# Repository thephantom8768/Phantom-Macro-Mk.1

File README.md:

# Phantom Macro Mk.1 Series

> A modular, snap-together macropad ecosystem with lateral pogo-pin bus interconnects.

Chain modules side-by-side to expand your desktop workflow—from a compact macro-pad into a full fledge keyboard.

---

## 📌 Project Status

- **Hardware:** Series still in-dev
- **Firmware:** In active development.
- **Interconnect:** Custom edge-mount 8 pin pogo interface.

---

## ⚡ Features

- **Snap & Chain Topology:** Expand your layout horizontally by mating adjacent modules using edge-mounted pogo connectors.
- **Unified Bus Standard:** Standardized power, ground, and communication rails allow any Mk.1-series compatible module to hot-mate with the system.
- **Flexible Layouts:** Mix and match different form factors (numpads, macro clusters, encoder dials) without rerunning separate USB cables to your host machine.

## ⚠️ Build Warnings

> **DIY Soldering Required:** This is a fully self-assembled project. It is not a plug-and-play kit and requires intermediate soldering experience.

* **Double-Sided Assembly:** Depending on the macro-pad, components might need to be soldered onto **both the top and bottom** of the PCB.

## *Mk.1 Series*

<details>
  <summary><b>🔢 Phantom-Macro-Mk.1 Pad (click here)</b></summary>
  
  ### Macro Mk.1 Pad
  
  #### Schematic

<table>
  <tr>
    <td colspan="4">
      
    </td>
  </tr>
</table>

#### PCB Layout

4 Layers PCB
| Front (1st layer)|Back (4th layer) |
| ----- | ----- |
|  |  |

#### PCB
| Front | Back |
| ----- | ---- |
|  |  |
|  |  |

#### Case

</details>

<details>
  <summary><b>🎹 Phantom-Macro-Mk.1 MIDI (click here)</b></summary>
  
  ### Macro Mk.1 MIDI
  
  #### Schematic

  ### PCB Layout 

  2 Layers PCB
  | Front | Back |
  | ----- | ----- |
  |  |  |

  #### PCB
  | Front | Back |
  | ----- | ---- |
  |  |  |
  |  |  |

</details>

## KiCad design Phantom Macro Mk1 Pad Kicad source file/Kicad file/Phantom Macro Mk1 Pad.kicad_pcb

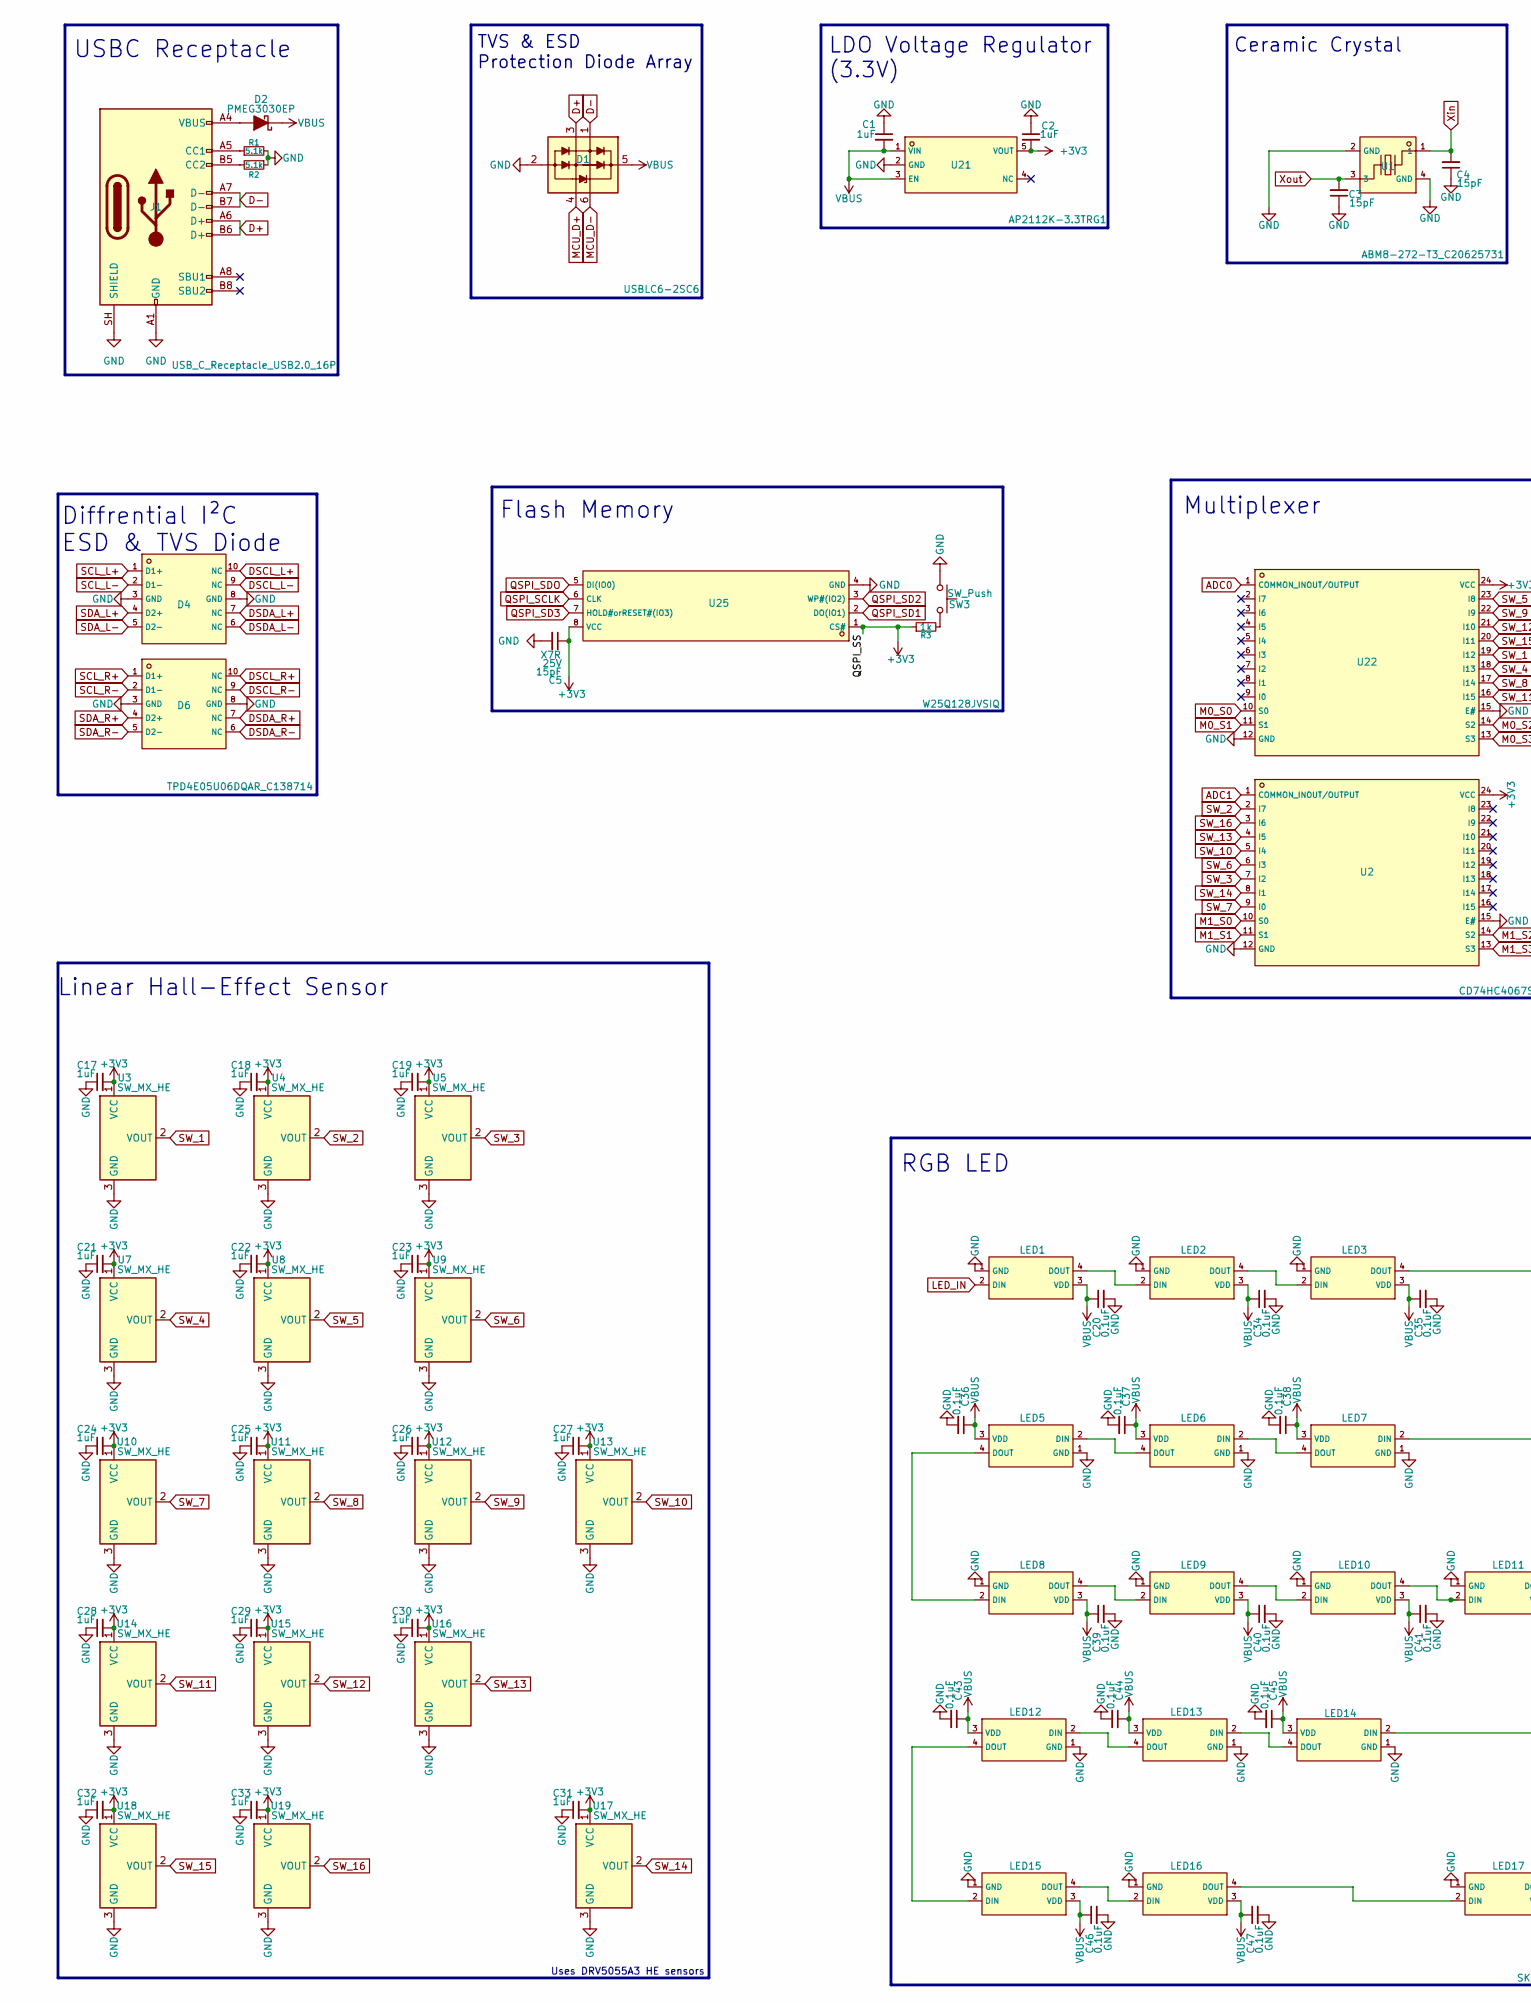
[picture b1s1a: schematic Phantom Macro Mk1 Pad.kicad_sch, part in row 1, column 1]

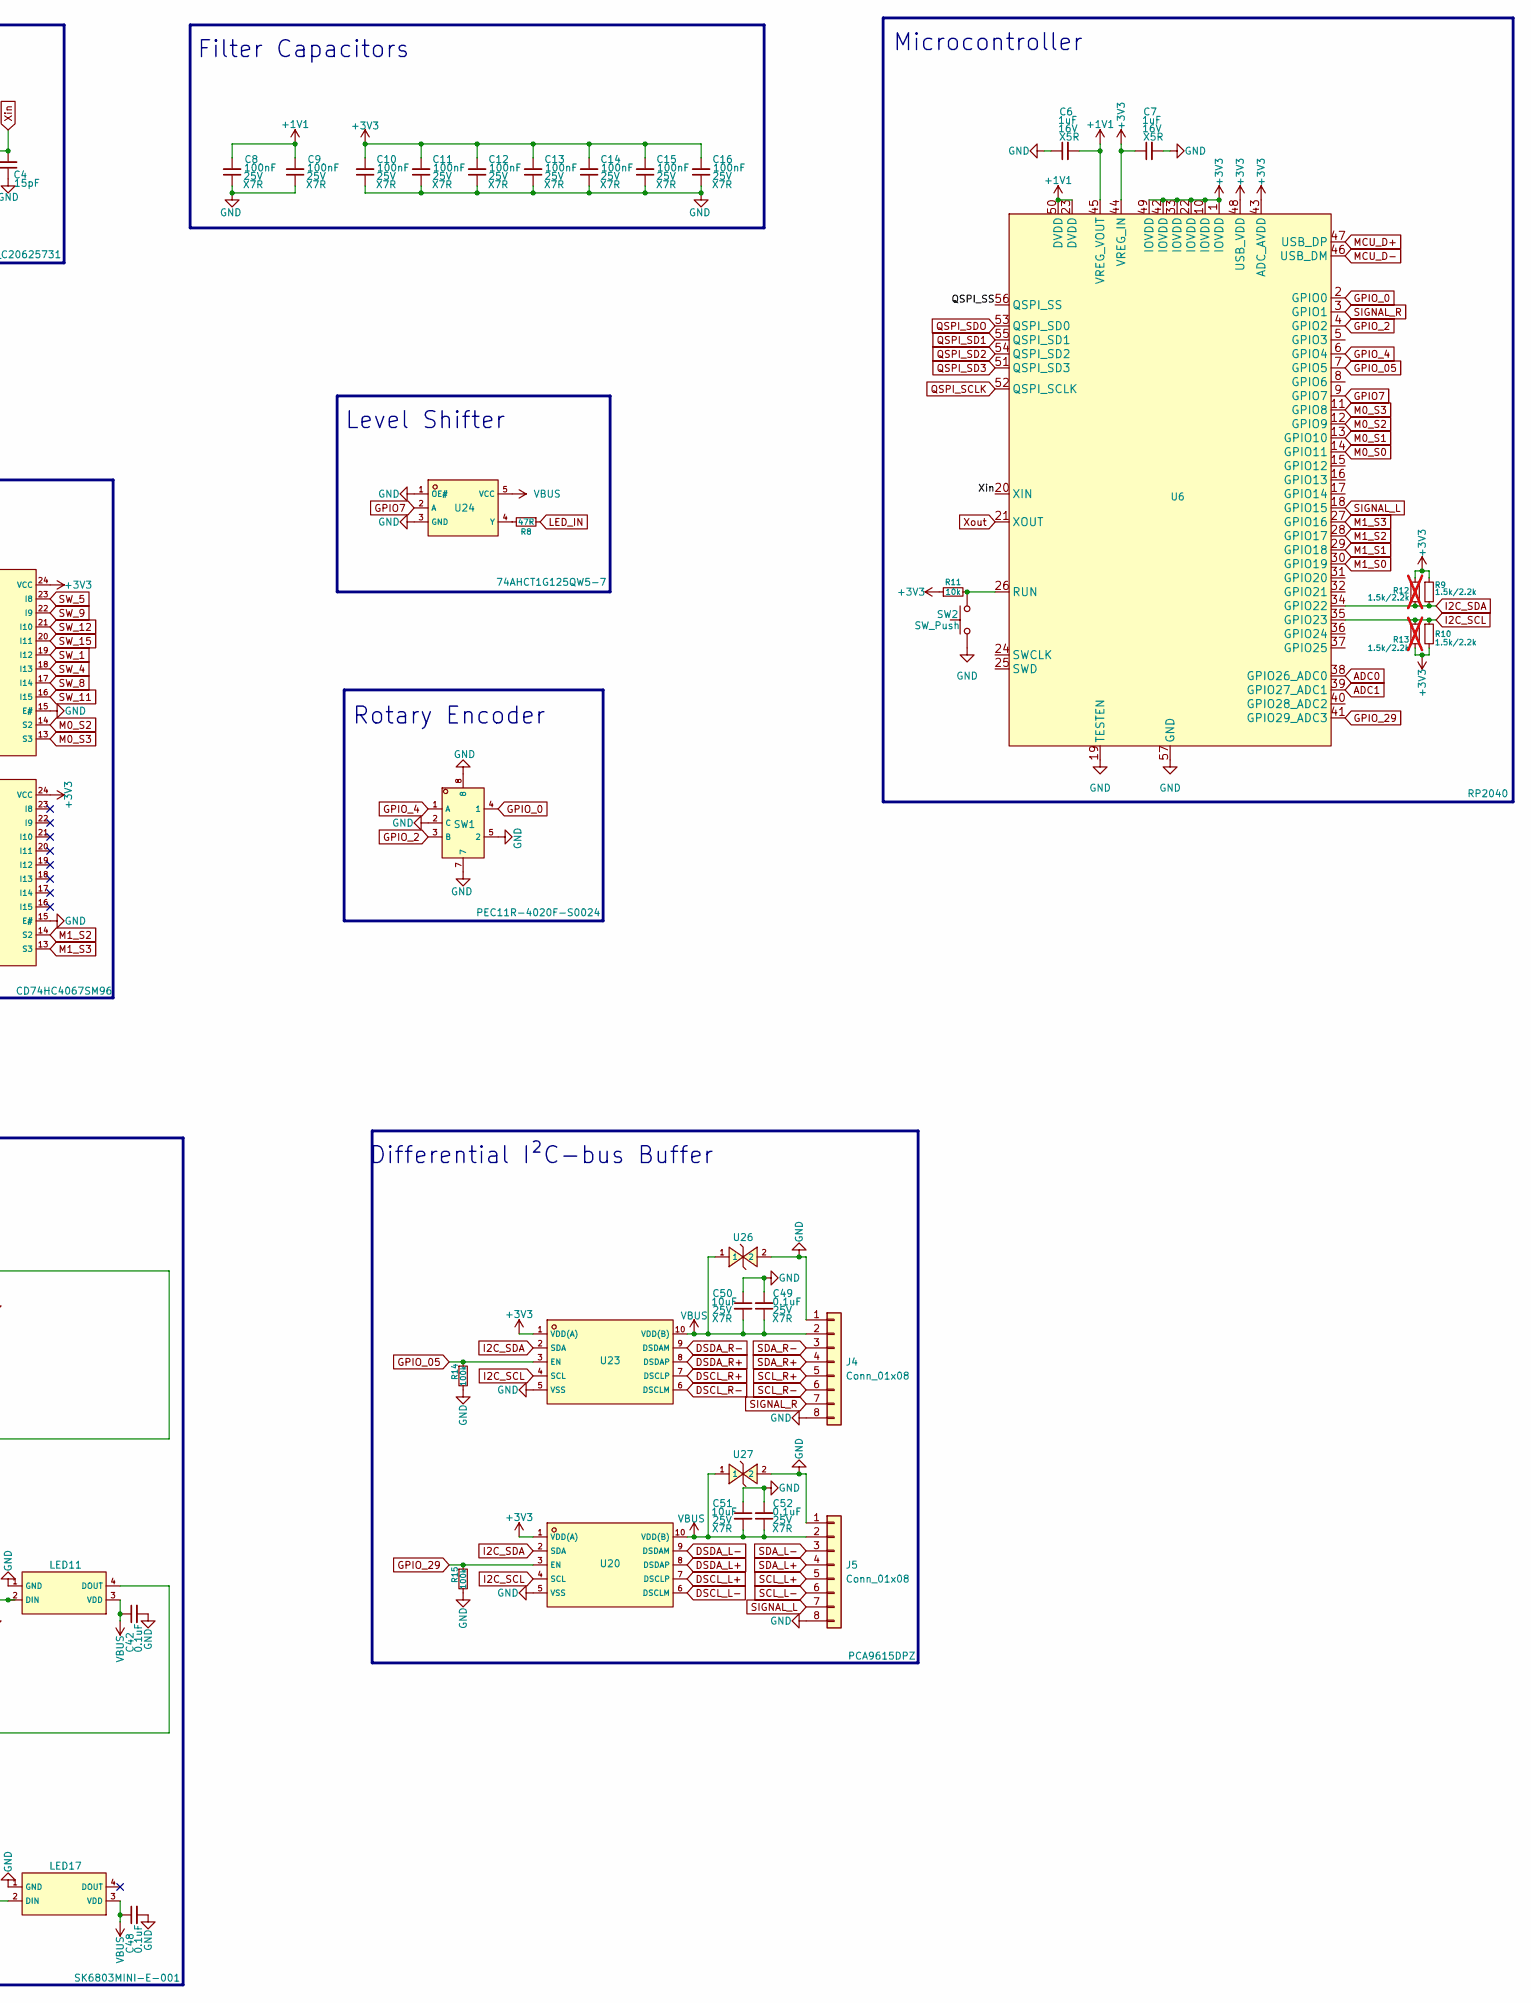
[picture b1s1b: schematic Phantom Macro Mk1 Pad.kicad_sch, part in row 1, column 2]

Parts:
C1, C2, C17, C18, C19, C21, C22, C23, C24, C25, C26, C27, C28, C29, C30, C31, C32, C33: 1uF; C_0603_1608Metric_Pad1.08x0.95mm_HandSolder
C3, C4: 15pF; C_0402_1005Metric_Pad0.74x0.62mm_HandSolder
C5: 15pF; C_0402_1005Metric_Pad0.74x0.62mm_HandSolder; Rating 25V
C6, C7: 1uF; C_0603_1608Metric_Pad1.08x0.95mm_HandSolder; Rating 16V
C8, C9, C10, C11, C12, C13, C14, C15, C16: 100nF; C_0402_1005Metric_Pad0.74x0.62mm_HandSolder; Rating 25V
C20, C34, C35, C36, C37, C38, C39, C40, C41, C42, C43, C44, C45, C46, C47, C48: 0.1uF; C_0603_1608Metric_Pad1.08x0.95mm_HandSolder
C49, C52: 0.1uF; C_0805_2012Metric_Pad1.18x1.45mm_HandSolder; Rating 25V
C50, C51: 10uF; C_0805_2012Metric_Pad1.18x1.45mm_HandSolder; Rating 25V
D1: USBLC6-2SC6; SOT-23-6
D2: PMEG3030EP; D_SOD-128
D4, D6: TPD4E05U06DQAR_C138714; C138714_USON-10_L2_5-W1_0-P0_50-BL; LCSC C138714
J1: USB_C_Receptacle_USB2.0_16P; USB_C_Receptacle_GCT_USB4110
J4, J5: Conn_01x08; PinHeader_1x08_P2.54mm_Horizontal
LED1, LED2, LED3, LED5, LED6, LED7, LED8, LED9, LED10, LED11, LED12, LED13, LED14, LED15, LED16, LED17: SK6803MINI-E-001; C5242955_LED-SMD_4P-L3_2-W2_8_SK6803MINI-E-001; LCSC C5242955
R1, R2: 5.1k; R_0402_1005Metric_Pad0.72x0.64mm_HandSolder
R3: 1k; R_0402_1005Metric_Pad0.72x0.64mm_HandSolder
R8: 47R; R_0402_1005Metric_Pad0.72x0.64mm_HandSolder
R9, R10: 1.5k/2.2k; R_0402_1005Metric_Pad0.72x0.64mm_HandSolder
R11: 10k; R_0402_1005Metric_Pad0.72x0.64mm_HandSolder
R12, R13: 1.5k/2.2k; R_0402_1005Metric_Pad0.72x0.64mm_HandSolder; not fitted
R14, R15: 100k; R_0402_1005Metric_Pad0.72x0.64mm_HandSolder
SW1: PEC11R-4020F-S0024; C143788_SW-TH_5P-L12_5-W13_4-P2_50-LS14_5; LCSC C143788
SW2, SW3: SW_Push; SW_SPST_B3U-1000P
U1: ABM8-272-T3_C20625731; C20625731_CRYSTAL-SMD_4P-L3_2-W2_5-BL; LCSC C20625731
U2, U22: CD74HC4067SM96; C98457_SSOP-24_L8_1-W5_3-P0_65-LS7_8-BL; LCSC C98457
U3, U4, U5, U7, U8, U9, U10, U11, U12, U13, U14, U15, U16, U17, U18, U19: SW_MX_HE; Haimu Dove H V2
U6: RP2040; C2040_LQFN-56_L7_0-W7_0-P0_4-EP; LCSC C2040
U20, U23: PCA9615DPZ; C3824272_TSSOP-10_L3_0-W3_0-P0_50-LS4_9-BL; LCSC C3824272
U21: AP2112K-3.3TRG1; C51118_SOT-25-5_L2_9-W1_6-P0_95-LS2_8-BL; LCSC C51118
U24: 74AHCT1G125QW5-7; C3755013_SOT-753_L3_1-W1_7-P0_95-LS3_0-BR; LCSC C3755013
U25: W25Q128JVSIQ; C113767_SOIC-8_L5_3-W5_3-P1_27-LS8_0-BL; LCSC C113767
U26, U27: TPD1E10B06DPYR; C48260_X1SON-2_L1_0-W0_6-P0_65-BI-1; LCSC C48260

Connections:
+1V1: C6.2, C8.2, C9.2, U6.23 (DVDD), U6.45 (VREG_VOUT), U6.50 (DVDD)
+3V3: C2.2, C5.1, C7.1, C10.2, C11.2, C12.2, C13.2, C14.2, C15.2, C16.2, C17.2, C18.2, C19.2, C21.2, C22.2, C23.2, C24.2, C25.2, C26.2, C27.2, C28.2, C29.2, C30.2, C31.2, C32.2, C33.2, R3.1, R9.1, R10.2, R11.1, R12.1, R13.2, U2.24 (VCC), U3.1 (VCC), U4.1 (VCC), U5.1 (VCC), U6.1 (IOVDD), U6.10 (IOVDD), U6.22 (IOVDD), U6.33 (IOVDD), U6.42 (IOVDD), U6.43 (ADC_AVDD), U6.44 (VREG_IN), U6.48 (USB_VDD), U6.49 (IOVDD), U6.56 (QSPI_SS), U7.1 (VCC), U8.1 (VCC), U9.1 (VCC), U10.1 (VCC), U11.1 (VCC), U12.1 (VCC), U13.1 (VCC), U14.1 (VCC), U15.1 (VCC), U16.1 (VCC), U17.1 (VCC), U18.1 (VCC), U19.1 (VCC), U20.1 (VDD(A)), U21.5 (VOUT), U22.24 (VCC), U23.1 (VDD(A)), U25.1 (CS#), U25.8 (VCC)
ADC0: U6.38 (GPIO26_ADC0), U22.1 (COMMON_INOUT/OUTPUT)
ADC1: U2.1 (COMMON_INOUT/OUTPUT), U6.39 (GPIO27_ADC1)
D+: D1.3 (L2), J1.A6 (D+), J1.B6 (D+)
D-: D1.1 (L1), J1.A7 (D-), J1.B7 (D-)
DSCL_L+: D4.10 (NC), U20.7 (DSCLP)
DSCL_L-: D4.9 (NC), U20.6 (DSCLM)
DSCL_R+: D6.10 (NC), U23.7 (DSCLP)
DSCL_R-: D6.9 (NC), U23.6 (DSCLM)
DSDA_L+: D4.7 (NC), U20.8 (DSDAP)
DSDA_L-: D4.6 (NC), U20.9 (DSDAM)
DSDA_R+: D6.7 (NC), U23.8 (DSDAP)
DSDA_R-: D6.6 (NC), U23.9 (DSDAM)
GND: C1.1, C2.1, C3.1, C4.1, C5.2, C6.1, C7.2, C8.1, C9.1, C10.1, C11.1, C12.1, C13.1, C14.1, C15.1, C16.1, C17.1, C18.1, C19.1, C20.2, C21.1, C22.1, C23.1, C24.1, C25.1, C26.1, C27.1, C28.1, C29.1, C30.1, C31.1, C32.1, C33.1, C34.2, C35.2, C36.2, C37.2, C38.2, C39.2, C40.2, C41.2, C42.2, C43.2, C44.2, C45.2, C46.2, C47.2, C48.2, C49.2, C50.1, C51.1, C52.2, D1.2 (VN), D4.3 (GND), D4.8 (GND), D6.3 (GND), D6.8 (GND), J1.A1 (GND), J1.A12 (GND), J1.B1 (GND), J1.B12 (GND), J1.SH (SHIELD), J4.1, J4.8, J5.1, J5.8, LED1.1 (GND), LED2.1 (GND), LED3.1 (GND), LED5.1 (GND), LED6.1 (GND), LED7.1 (GND), LED8.1 (GND), LED9.1 (GND), LED10.1 (GND), LED11.1 (GND), LED12.1 (GND), LED13.1 (GND), LED14.1 (GND), LED15.1 (GND), LED16.1 (GND), LED17.1 (GND), R1.2, R2.1, R14.2, R15.2, SW1.2 (C), SW1.5 (2), SW1.7, SW1.8, SW2.1, SW3.1, U1.2 (GND), U1.4 (GND), U2.12 (GND), U2.15 (E#), U3.3 (GND), U4.3 (GND), U5.3 (GND), U6.19 (TESTEN), U6.57 (GND), U7.3 (GND), U8.3 (GND), U9.3 (GND), U10.3 (GND), U11.3 (GND), U12.3 (GND), U13.3 (GND), U14.3 (GND), U15.3 (GND), U16.3 (GND), U17.3 (GND), U18.3 (GND), U19.3 (GND), U20.5 (VSS), U21.2 (GND), U22.12 (GND), U22.15 (E#), U23.5 (VSS), U24.1 (OE#), U24.3 (GND), U25.4 (GND), U26.2, U27.2
GPIO7: U6.9 (GPIO7), U24.2 (A)
GPIO_0: SW1.4 (1), U6.2 (GPIO0)
GPIO_2: SW1.3 (B), U6.4 (GPIO2)
GPIO_4: SW1.1 (A), U6.6 (GPIO4)
GPIO_05: R14.1, U6.7 (GPIO5), U23.3 (EN)
GPIO_29: R15.1, U6.41 (GPIO29_ADC3), U20.3 (EN)
I2C_SCL: R10.1, R13.1, U6.35 (GPIO23), U20.4 (SCL), U23.4 (SCL)
I2C_SDA: R9.2, R12.2, U6.34 (GPIO22), U20.2 (SDA), U23.2 (SDA)
LED_IN: LED1.2 (DIN), R8.1
M0_S0: U6.14 (GPIO11), U22.10 (S0)
M0_S1: U6.13 (GPIO10), U22.11 (S1)
M0_S2: U6.12 (GPIO9), U22.14 (S2)
M0_S3: U6.11 (GPIO8), U22.13 (S3)
M1_S0: U2.10 (S0), U6.30 (GPIO19)
M1_S1: U2.11 (S1), U6.29 (GPIO18)
M1_S2: U2.14 (S2), U6.28 (GPIO17)
M1_S3: U2.13 (S3), U6.27 (GPIO16)
MCU_D+: D1.4 (L2), U6.47 (USB_DP)
MCU_D-: D1.6 (L1), U6.46 (USB_DM)
unnamed: D2.2 (A), J1.A4 (VBUS), J1.A9 (VBUS), J1.B4 (VBUS), J1.B9 (VBUS)
unnamed: J1.A5 (CC1), R1.1
unnamed: J1.B5 (CC2), R2.2
unnamed: LED1.4 (DOUT), LED2.2 (DIN)
unnamed: LED2.4 (DOUT), LED3.2 (DIN)
unnamed: LED3.4 (DOUT), LED7.2 (DIN)
unnamed: LED5.2 (DIN), LED6.4 (DOUT)
unnamed: LED5.4 (DOUT), LED8.2 (DIN)
unnamed: LED6.2 (DIN), LED7.4 (DOUT)
unnamed: LED8.4 (DOUT), LED9.2 (DIN)
unnamed: LED9.4 (DOUT), LED10.2 (DIN)
unnamed: LED10.4 (DOUT), LED11.2 (DIN)
unnamed: LED11.4 (DOUT), LED14.2 (DIN)
unnamed: LED12.2 (DIN), LED13.4 (DOUT)
unnamed: LED12.4 (DOUT), LED15.2 (DIN)
unnamed: LED13.2 (DIN), LED14.4 (DOUT)
unnamed: LED15.4 (DOUT), LED16.2 (DIN)
unnamed: LED16.4 (DOUT), LED17.2 (DIN)
unnamed: R3.2, SW3.2
unnamed: R11.2, SW2.2, U6.26 (RUN)
unnamed: R8.2, U24.4 (Y)
QSPI_SCLK: U6.52 (QSPI_SCLK), U25.6 (CLK)
QSPI_SD1: U6.55 (QSPI_SD1), U25.2 (DO(IO1))
QSPI_SD2: U6.54 (QSPI_SD2), U25.3 (WP#(IO2))
QSPI_SD3: U6.51 (QSPI_SD3), U25.7 (HOLD#orRESET#(IO3))
QSPI_SDO: U6.53 (QSPI_SD0), U25.5 (DI(IO0))
SCL_L+: D4.1 (D1+), J5.5
SCL_L-: D4.2 (D1-), J5.6
SCL_R+: D6.1 (D1+), J4.5
SCL_R-: D6.2 (D1-), J4.6
SDA_L+: D4.4 (D2+), J5.4
SDA_L-: D4.5 (D2-), J5.3
SDA_R+: D6.4 (D2+), J4.4
SDA_R-: D6.5 (D2-), J4.3
SIGNAL_L: J5.7, U6.18 (GPIO15)
SIGNAL_R: J4.7, U6.3 (GPIO1)
SW_1: U3.2 (VOUT), U22.19 (I12)
SW_2: U2.2 (I7), U4.2 (VOUT)
SW_3: U2.7 (I2), U5.2 (VOUT)
SW_4: U7.2 (VOUT), U22.18 (I13)
SW_5: U8.2 (VOUT), U22.23 (I8)
SW_6: U2.6 (I3), U9.2 (VOUT)
SW_7: U2.9 (I0), U10.2 (VOUT)
SW_8: U11.2 (VOUT), U22.17 (I14)
SW_9: U12.2 (VOUT), U22.22 (I9)
SW_10: U2.5 (I4), U13.2 (VOUT)
SW_11: U14.2 (VOUT), U22.16 (I15)
SW_12: U15.2 (VOUT), U22.21 (I10)
SW_13: U2.4 (I5), U16.2 (VOUT)
SW_14: U2.8 (I1), U17.2 (VOUT)
SW_15: U18.2 (VOUT), U22.20 (I11)
SW_16: U2.3 (I6), U19.2 (VOUT)
VBUS: C1.2, C20.1, C34.1, C35.1, C36.1, C37.1, C38.1, C39.1, C40.1, C41.1, C42.1, C43.1, C44.1, C45.1, C46.1, C47.1, C48.1, C49.1, C50.2, C51.2, C52.1, D1.5 (VP), D2.1 (K), J4.2, J5.2, LED1.3 (VDD), LED2.3 (VDD), LED3.3 (VDD), LED5.3 (VDD), LED6.3 (VDD), LED7.3 (VDD), LED8.3 (VDD), LED9.3 (VDD), LED10.3 (VDD), LED11.3 (VDD), LED12.3 (VDD), LED13.3 (VDD), LED14.3 (VDD), LED15.3 (VDD), LED16.3 (VDD), LED17.3 (VDD), U20.10 (VDD(B)), U21.1 (VIN), U21.3 (EN), U23.10 (VDD(B)), U24.5 (VCC), U26.1, U27.1
Xin: C4.2, U1.1, U6.20 (XIN)
Xout: C3.2, U1.3, U6.21 (XOUT)

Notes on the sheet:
LDO Voltage Regulator (3.3V)
RGB LED
Flash Memory
Multiplexer
Filter Capacitors
Ceramic Crystal
Level Shifter
Rotary Encoder
TVS & ESD Protection Diode Array
Uses DRV5055A3 HE sensors
Microcontroller
Linear Hall-Effect Sensor
Differential I²C-bus Buffer
Diffrential I²C ESD & TVS Diode
USBC Receptacle

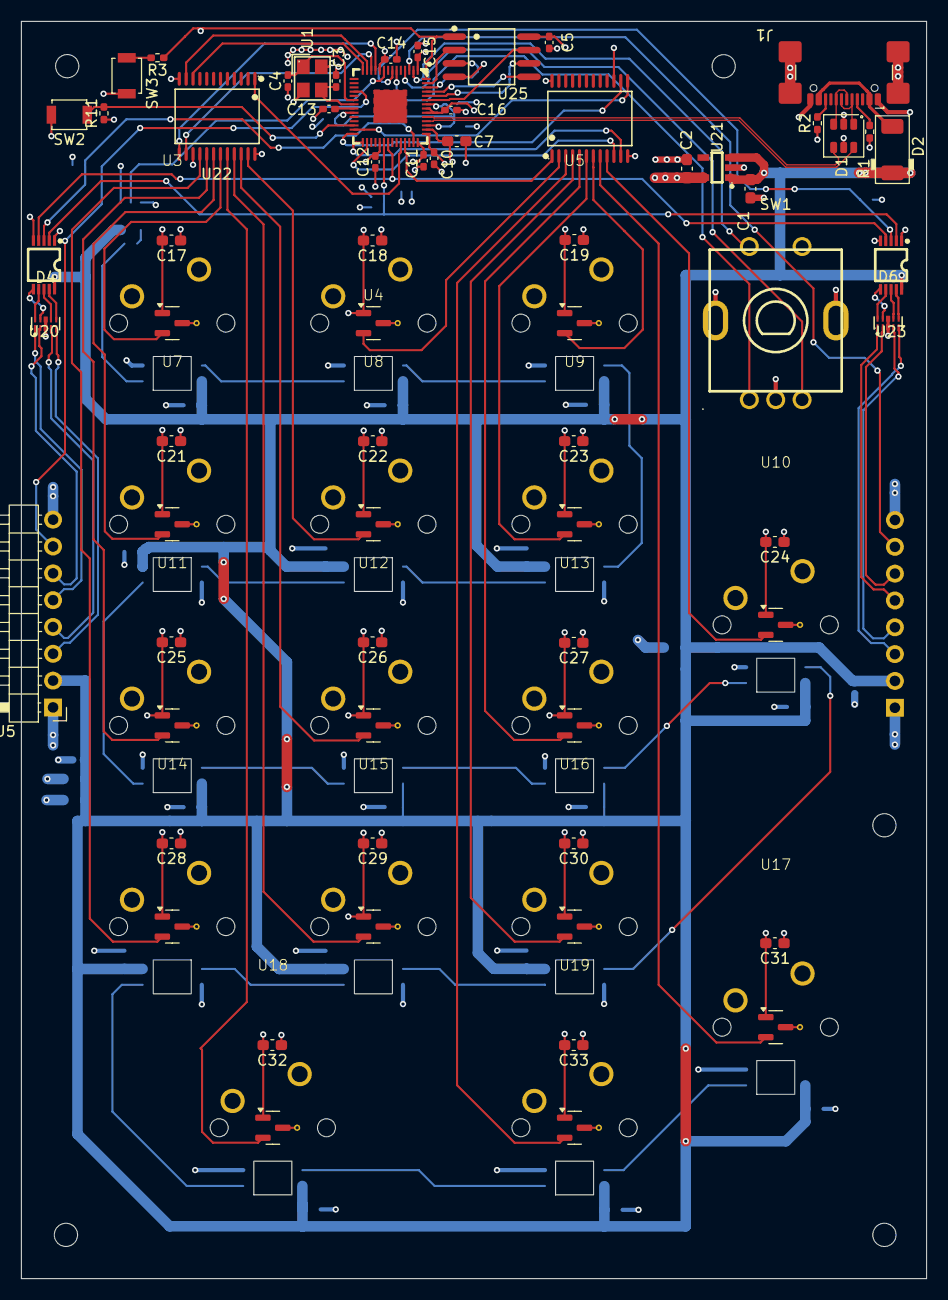
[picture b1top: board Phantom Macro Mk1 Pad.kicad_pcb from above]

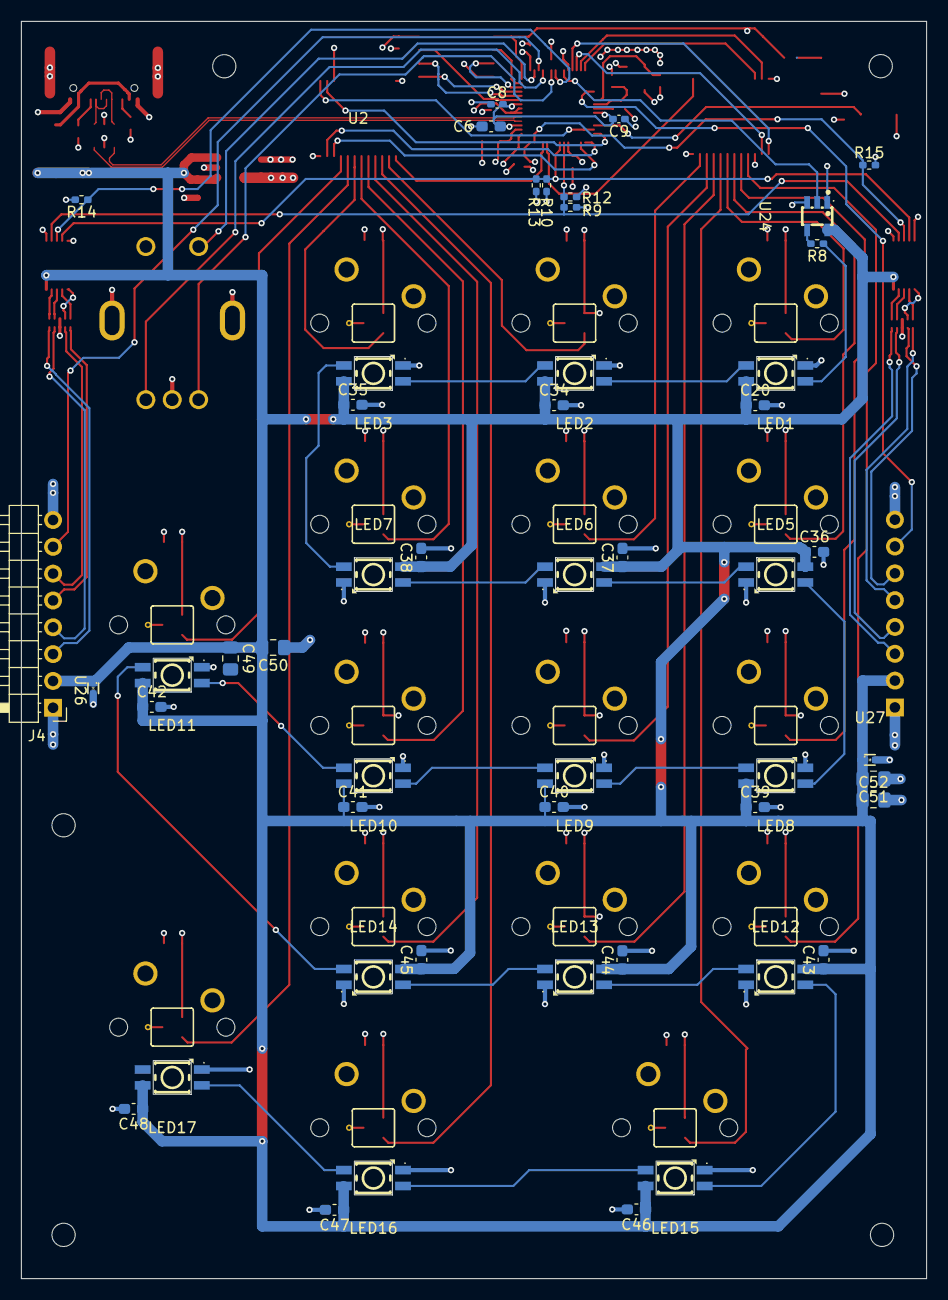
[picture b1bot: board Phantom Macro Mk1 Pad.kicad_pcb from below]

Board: 4 copper layers, 85.7 x 119.1 mm, 116 parts (50 on the bottom side), 89 nets.

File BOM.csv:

"Reference","Qty","Value","DNP","Exclude from BOM","Exclude from Board","Footprint","Datasheet"
"C1,C2,C6,C7,C17,C18,C19,C21,C22,C23,C24,C25,C26,C27,C28,C29,C30,C31,C32,C33","20","1uF","","","","Capacitor_SMD:C_0603_1608Metric_Pad1.08x0.95mm_HandSolder",""
"C3,C4,C5","3","15pF","","","","Capacitor_SMD:C_0402_1005Metric_Pad0.74x0.62mm_HandSolder",""
"C8,C9,C10,C11,C12,C13,C14,C15,C16","9","100nF","","","","Capacitor_SMD:C_0402_1005Metric_Pad0.74x0.62mm_HandSolder",""
"D1","1","USBLC6-2SC6","","","","PCM_Package_TO_SOT_SMD_AKL:SOT-23-6","https://www.tme.eu/Document/db59d28d28a96c34f26d05f234ff409c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"
"D2","1","PMEG3030EP","","","","PCM_Diode_SMD_AKL:D_SOD-128","https://www.tme.eu/Document/abe71b1e3ae43c8e032df0d278a6f86a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"
"J1","1","USB_C_Receptacle_USB2.0_16P","","","","Connector_USB:USB_C_Receptacle_GCT_USB4110","https://www.usb.org/sites/default/files/documents/usb_type-c.zip"
"J2","1","Conn_01x02","","","","Connector_PinSocket_2.54mm:PinSocket_1x02_P2.54mm_Vertical",""
"J4,J5","2","Conn_01x08","","","","Connector_PinHeader_2.54mm:PinHeader_1x08_P2.54mm_Horizontal",""
"LED1,LED2,LED3,LED5,LED6,LED7,LED8,LED9,LED10,LED11,LED12,LED13,LED14,LED15,LED16,LED17","16","SK6803MINI-E-001","","","","lcsc_shared_footprints:C5242955_LED-SMD_4P-L3_2-W2_8_SK6803MINI-E-001","https://wmsc.lcsc.com/wmsc/upload/file/pdf/v2/lcsc/221101150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"
"Q1,Q2","2","2N7002 7002","","","","lcsc_shared_footprints:C8545_SOT-23-3_L2_9-W1_3-P1_90-LS2_4-BR","https://www.lcsc.com/datasheet/lcsc_datasheet_2304140030_Jia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"
"R1,R2","2","5.1k","","","","Resistor_SMD:R_0402_1005Metric_Pad0.72x0.64mm_HandSolder",""
"R3","1","1k","","","","Resistor_SMD:R_0402_1005Metric_Pad0.72x0.64mm_HandSolder",""
"R4,R5","2","10k","","","","Resistor_SMD:R_0402_1005Metric_Pad0.72x0.64mm_HandSolder",""
"R6,R7","2","120R","","","","Resistor_SMD:R_0402_1005Metric_Pad0.72x0.64mm_HandSolder",""
"SW1","1","PEC11R-4020F-S0024","","","","lcsc_shared_footprints:C143788_SW-TH_5P-L12_5-W13_4-P2_50-LS14_5","https://www.lcsc.com/datasheet/lcsc_datasheet_2304140030_BOU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"
"U1","1","ABM8-272-T3_C20625731","","","","lcsc_shared_footprints:C20625731_CRYSTAL-SMD_4P-L3_2-W2_5-BL","https://www.lcsc.com/datasheet/lcsc_datasheet_2410121909_Abr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"
"U2,U22","2","CD74HC4067SM96","","","","lcsc_shared_footprints:C98457_SSOP-24_L8_1-W5_3-P0_65-LS7_8-BL","https://www.lcsc.com/datasheet/lcsc_datasheet_1810010611_Tex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"
"U3,U4,U5,U7,U8,U9,U10,U11,U12,U13,U14,U15,U16,U17,U18,U19","16","SW_MX_HE","","","","PCM_marbastlib-he:Haimu Dove H V2","https://wmsc.lcsc.com/wmsc/upload/file/pdf/v2/lcsc/231027181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"
"U6","1","RP2040","","","","lcsc_shared_footprints:C2040_LQFN-56_L7_0-W7_0-P0_4-EP","https://www.lcsc.com/datasheet/lcsc_datasheet_2201101600_Ras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"
"U20,U23","2","PCA9615DPZ","","","","lcsc_shared_footprints:C3824272_TSSOP-10_L3_0-W3_0-P0_50-LS4_9-BL","https://wmsc.lcsc.com/wmsc/upload/file/pdf/v2/lcsc/240708164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"
"U21","1","AP2112K-3.3TRG1","","","","lcsc_shared_footprints:C51118_SOT-25-5_L2_9-W1_6-P0_95-LS2_8-BL","https://www.lcsc.com/datasheet/lcsc_datasheet_2304140030_Dio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"
"U25","1","W25Q128JVSIQ","","","","lcsc_shared_footprints:C113767_SOIC-8_L5_3-W5_3-P1_27-LS8_0-BL","https://www.lcsc.com/datasheet/lcsc_datasheet_1912111437_Win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"
